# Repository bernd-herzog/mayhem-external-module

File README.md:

# mayhem-external-module
External Module for the HackRF+PortaPack H4

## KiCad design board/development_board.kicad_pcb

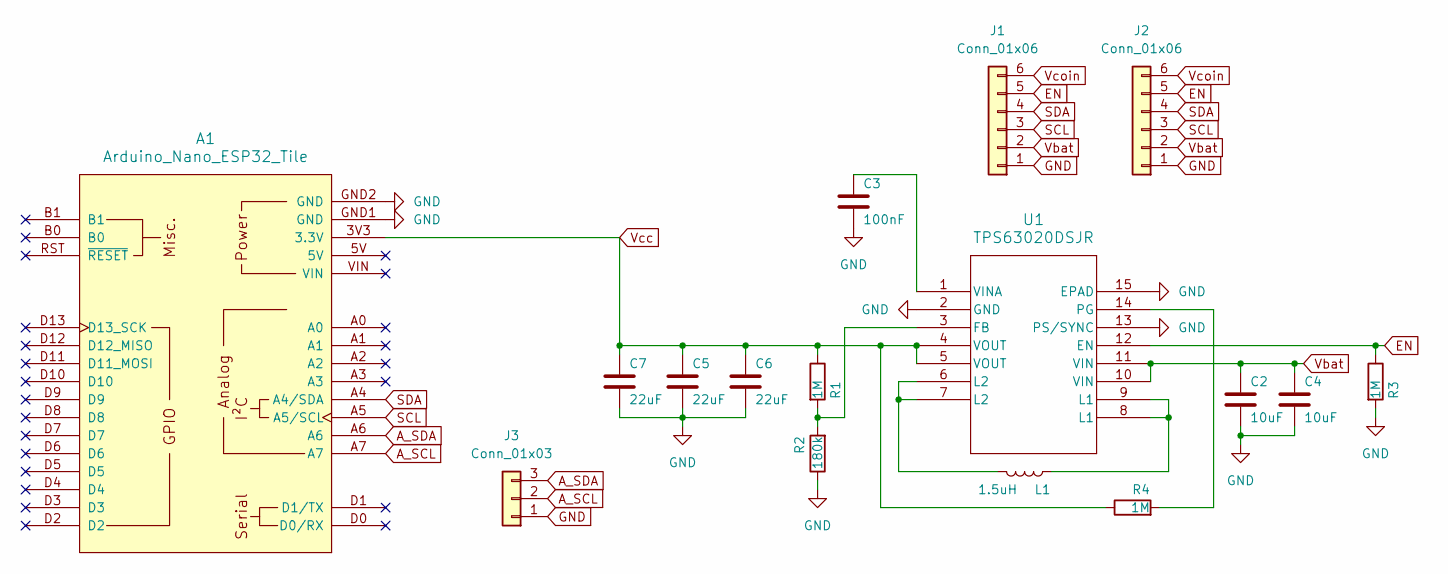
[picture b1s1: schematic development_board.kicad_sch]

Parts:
A1: Arduino_Nano_ESP32_Tile
C2, C4: 10uF; C_0603_1608Metric; Part CL10A106KP8NNNC; JLC 0603
C3: 100nF; C_0805_2012Metric; Part CC0805KRX7R9BB104; JLC 0805
C5, C6, C7: 22uF; C_0603_1608Metric; Part CL10A226MQ8NRNC; JLC 0603
J1, J2: Conn_01x06; External Module
J3: Conn_01x03; PinSocket_1x03_P2.54mm_Vertical
L1: 1.5uH; L_Taiyo-Yuden_NR-40xx; Part XFL4020-152MEC; JLC SMD,4x4mm
R1, R3, R4: 1M; R_0603_1608Metric; Part 0603WAF1004T5E; JLC 0603
R2: 180k; R_0603_1608Metric; Part 0603WAF1803T5E; JLC 0603
U1: TPS63020DSJR; DSJ14_2P85X1P58; Part TPS63020DSJR; JLC VSON-14-EP(3x4)

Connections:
A_SCL: A1.A7, J3.2
A_SDA: A1.A6, J3.3
EN: J1.5, J2.5, R3.1, U1.12 (EN)
GND: A1.GND1 (GND), A1.GND2 (GND), C2.2, C3.2, C4.2, C5.2, C6.2, C7.2, J1.1, J2.1, J3.1, R2.1, R3.2, U1.2 (GND), U1.13 (PS/SYNC), U1.15 (EPAD)
unnamed: L1.1, U1.8 (L1), U1.9 (L1)
unnamed: L1.2, U1.6 (L2), U1.7 (L2)
unnamed: R1.2, R2.2, U1.3 (FB)
unnamed: R4.2, U1.14 (PG)
unnamed: C3.1, U1.1 (VINA)
SCL: A1.A5 (A5/SCL), J1.3, J2.3
SDA: A1.A4 (A4/SDA), J1.4, J2.4
Vbat: C2.1, C4.1, J1.2, J2.2, U1.10 (VIN), U1.11 (VIN)
Vcc: A1.3V3 (3.3V), C5.1, C6.1, C7.1, R1.1, R4.1, U1.4 (VOUT), U1.5 (VOUT)
Vcoin: J1.6, J2.6

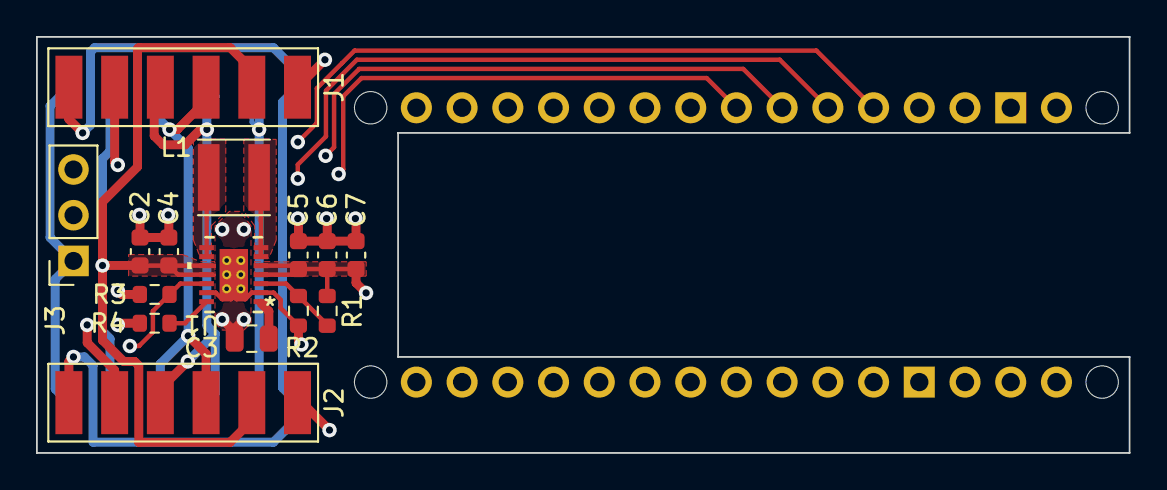
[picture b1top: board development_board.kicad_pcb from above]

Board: 4 copper layers, 60.7 x 23.1 mm, 16 parts (1 on the bottom side), 14 nets.

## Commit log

2024-10-04 added esp idf project
2024-10-07 i2c slave driver wip
2024-10-09 added view mirror api
2024-10-09 added pcb files
2024-10-10 implemented uart data transfer and display
2024-10-13 implemented standalone app touch event
2024-10-13 implemented focus management
2024-10-14 refactoring
